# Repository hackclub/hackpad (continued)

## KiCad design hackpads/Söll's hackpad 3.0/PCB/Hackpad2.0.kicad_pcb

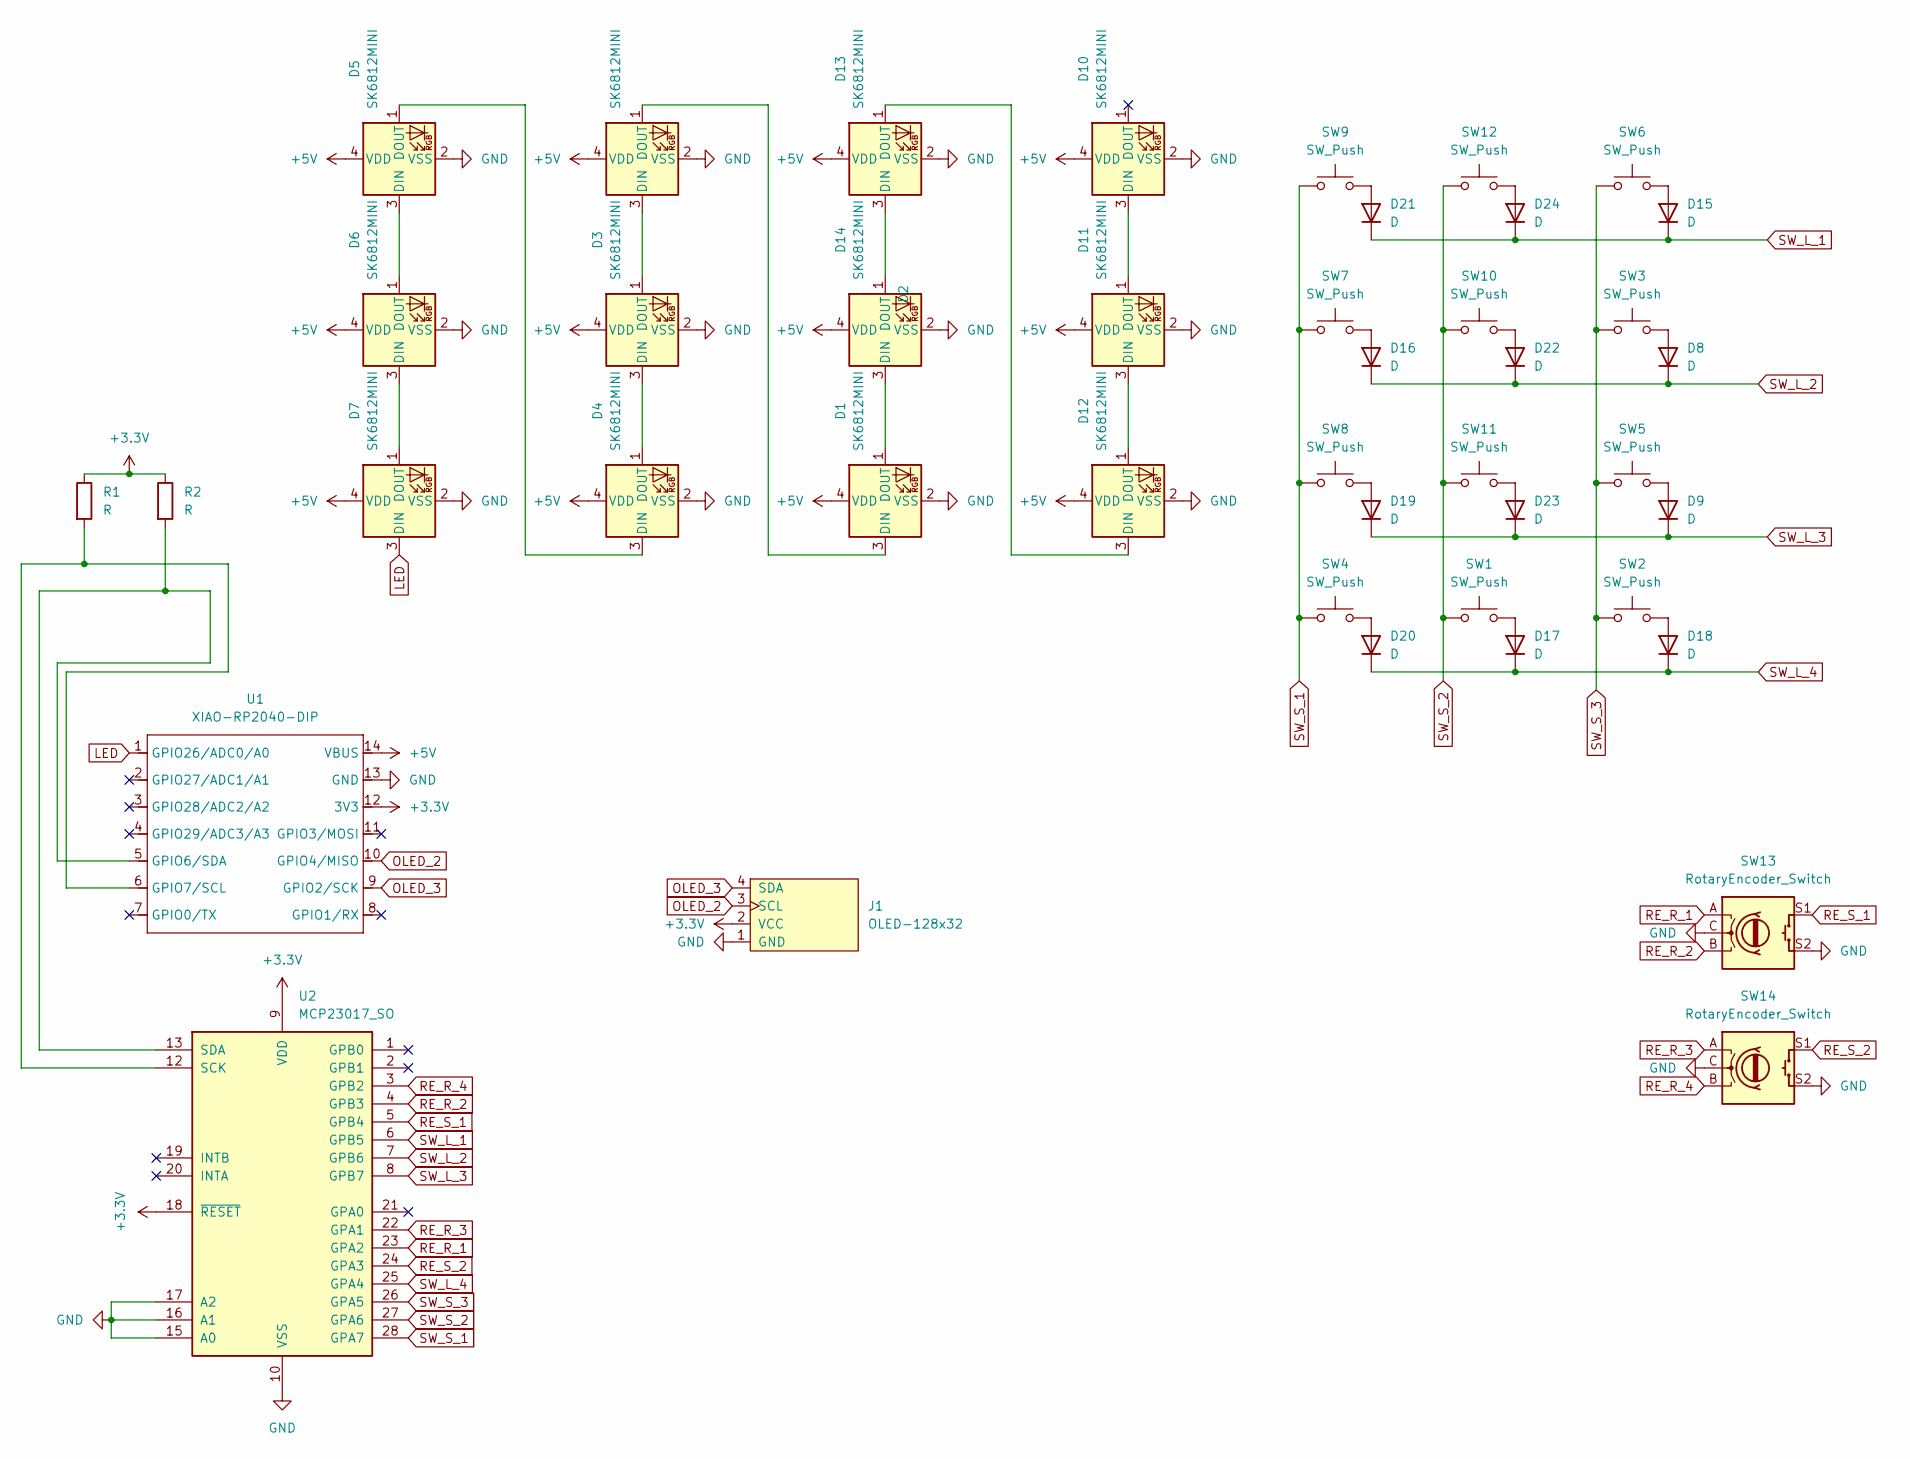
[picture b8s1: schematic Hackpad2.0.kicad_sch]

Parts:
D1, D2, D3, D4, D5, D6, D7, D10, D11, D12, D13, D14: SK6812MINI; LED_SK6812MINI_PLCC4_3.5x3.5mm_P1.75mm
D8, D9, D15, D16, D17, D18, D19, D20, D21, D22, D23, D24: D; D_DO-35_SOD27_P7.62mm_Horizontal
J1: OLED-128x32; SSD1306-0.91-OLED-4pin-128x32
R1, R2: R; R_Axial_DIN0204_L3.6mm_D1.6mm_P7.62mm_Horizontal
SW1, SW2, SW3, SW4, SW5, SW6, SW7, SW8, SW9, SW10, SW11, SW12: SW_Push; SW_Cherry_MX_1.00u_PCB
SW13, SW14: RotaryEncoder_Switch; RotaryEncoder_Alps_EC11E-Switch_Vertical_H20mm_CircularMoun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
U1: XIAO-RP2040-DIP
U2: MCP23017_SO; SOIC-28W_7.5x17.9mm_P1.27mm

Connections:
+3.3V: J1.2 (VCC), R1.1, R2.1, U1.12 (3V3), U2.9 (VDD), U2.18 (~RESET)
+5V: D1.4 (VDD), D2.4 (VDD), D3.4 (VDD), D4.4 (VDD), D5.4 (VDD), D6.4 (VDD), D7.4 (VDD), D10.4 (VDD), D11.4 (VDD), D12.4 (VDD), D13.4 (VDD), D14.4 (VDD), U1.14 (VBUS)
GND: D1.2 (VSS), D2.2 (VSS), D3.2 (VSS), D4.2 (VSS), D5.2 (VSS), D6.2 (VSS), D7.2 (VSS), D10.2 (VSS), D11.2 (VSS), D12.2 (VSS), D13.2 (VSS), D14.2 (VSS), J1.1 (GND), SW13.C, SW13.S2, SW14.C, SW14.S2, U1.13 (GND), U2.10 (VSS), U2.15 (A0), U2.16 (A1), U2.17 (A2)
LED: D7.3 (DIN), U1.1 (GPIO26/ADC0/A0)
unnamed: D1.3 (DIN), D2.1 (DOUT)
unnamed: D1.1 (DOUT), D14.3 (DIN)
unnamed: D2.3 (DIN), D3.1 (DOUT)
unnamed: D3.3 (DIN), D4.1 (DOUT)
unnamed: D4.3 (DIN), D5.1 (DOUT)
unnamed: D5.3 (DIN), D6.1 (DOUT)
unnamed: D6.3 (DIN), D7.1 (DOUT)
unnamed: D8.2 (A), SW3.2
unnamed: D9.2 (A), SW5.2
unnamed: D10.3 (DIN), D11.1 (DOUT)
unnamed: D11.3 (DIN), D12.1 (DOUT)
unnamed: D12.3 (DIN), D13.1 (DOUT)
unnamed: D13.3 (DIN), D14.1 (DOUT)
unnamed: D15.2 (A), SW6.2
unnamed: D16.2 (A), SW7.2
unnamed: D17.2 (A), SW1.2
unnamed: D18.2 (A), SW2.2
unnamed: D19.2 (A), SW8.2
unnamed: D20.2 (A), SW4.2
unnamed: D21.2 (A), SW9.2
unnamed: D22.2 (A), SW10.2
unnamed: D23.2 (A), SW11.2
unnamed: D24.2 (A), SW12.2
unnamed: R2.2, U1.5 (GPIO6/SDA), U2.13 (SDA)
unnamed: R1.2, U1.6 (GPIO7/SCL), U2.12 (SCK)
OLED_2: J1.3 (SCL), U1.10 (GPIO4/MISO)
OLED_3: J1.4 (SDA), U1.9 (GPIO2/SCK)
RE_R_1: SW13.A, U2.23 (GPA2)
RE_R_2: SW13.B, U2.4 (GPB3)
RE_R_3: SW14.A, U2.22 (GPA1)
RE_R_4: SW14.B, U2.3 (GPB2)
RE_S_1: SW13.S1, U2.5 (GPB4)
RE_S_2: SW14.S1, U2.24 (GPA3)
SW_L_1: D15.1 (K), D21.1 (K), D24.1 (K), U2.6 (GPB5)
SW_L_2: D8.1 (K), D16.1 (K), D22.1 (K), U2.7 (GPB6)
SW_L_3: D9.1 (K), D19.1 (K), D23.1 (K), U2.8 (GPB7)
SW_L_4: D17.1 (K), D18.1 (K), D20.1 (K), U2.25 (GPA4)
SW_S_1: SW4.1, SW7.1, SW8.1, SW9.1, U2.28 (GPA7)
SW_S_2: SW1.1, SW10.1, SW11.1, SW12.1, U2.27 (GPA6)
SW_S_3: SW2.1, SW3.1, SW5.1, SW6.1, U2.26 (GPA5)

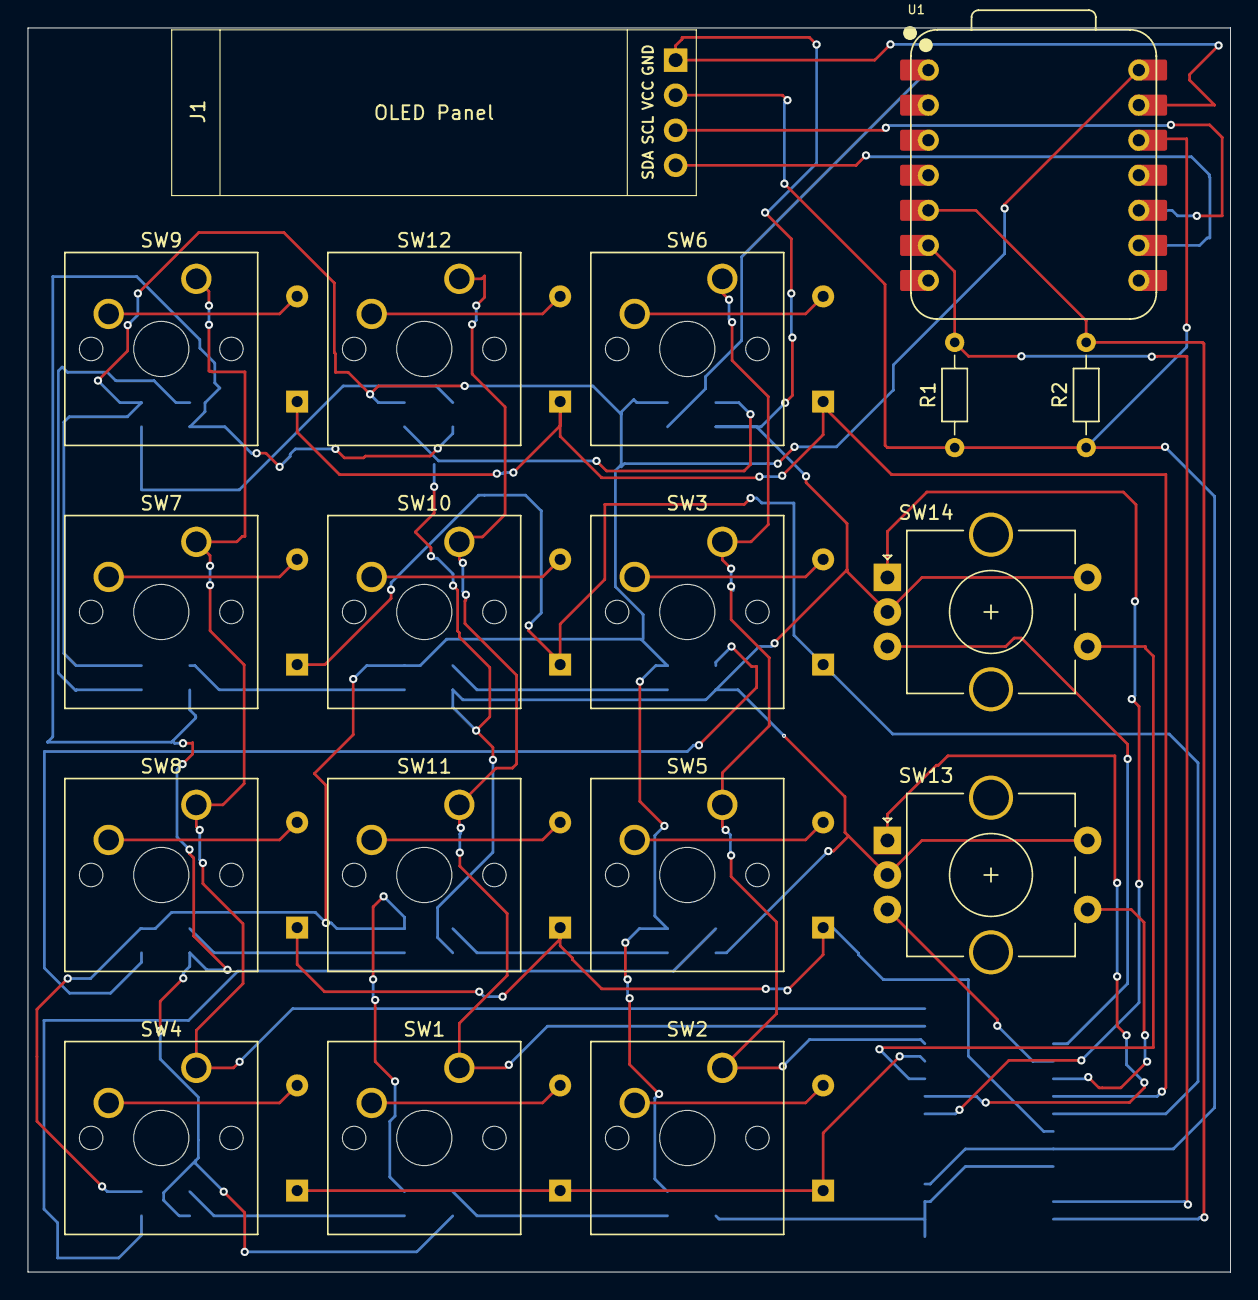
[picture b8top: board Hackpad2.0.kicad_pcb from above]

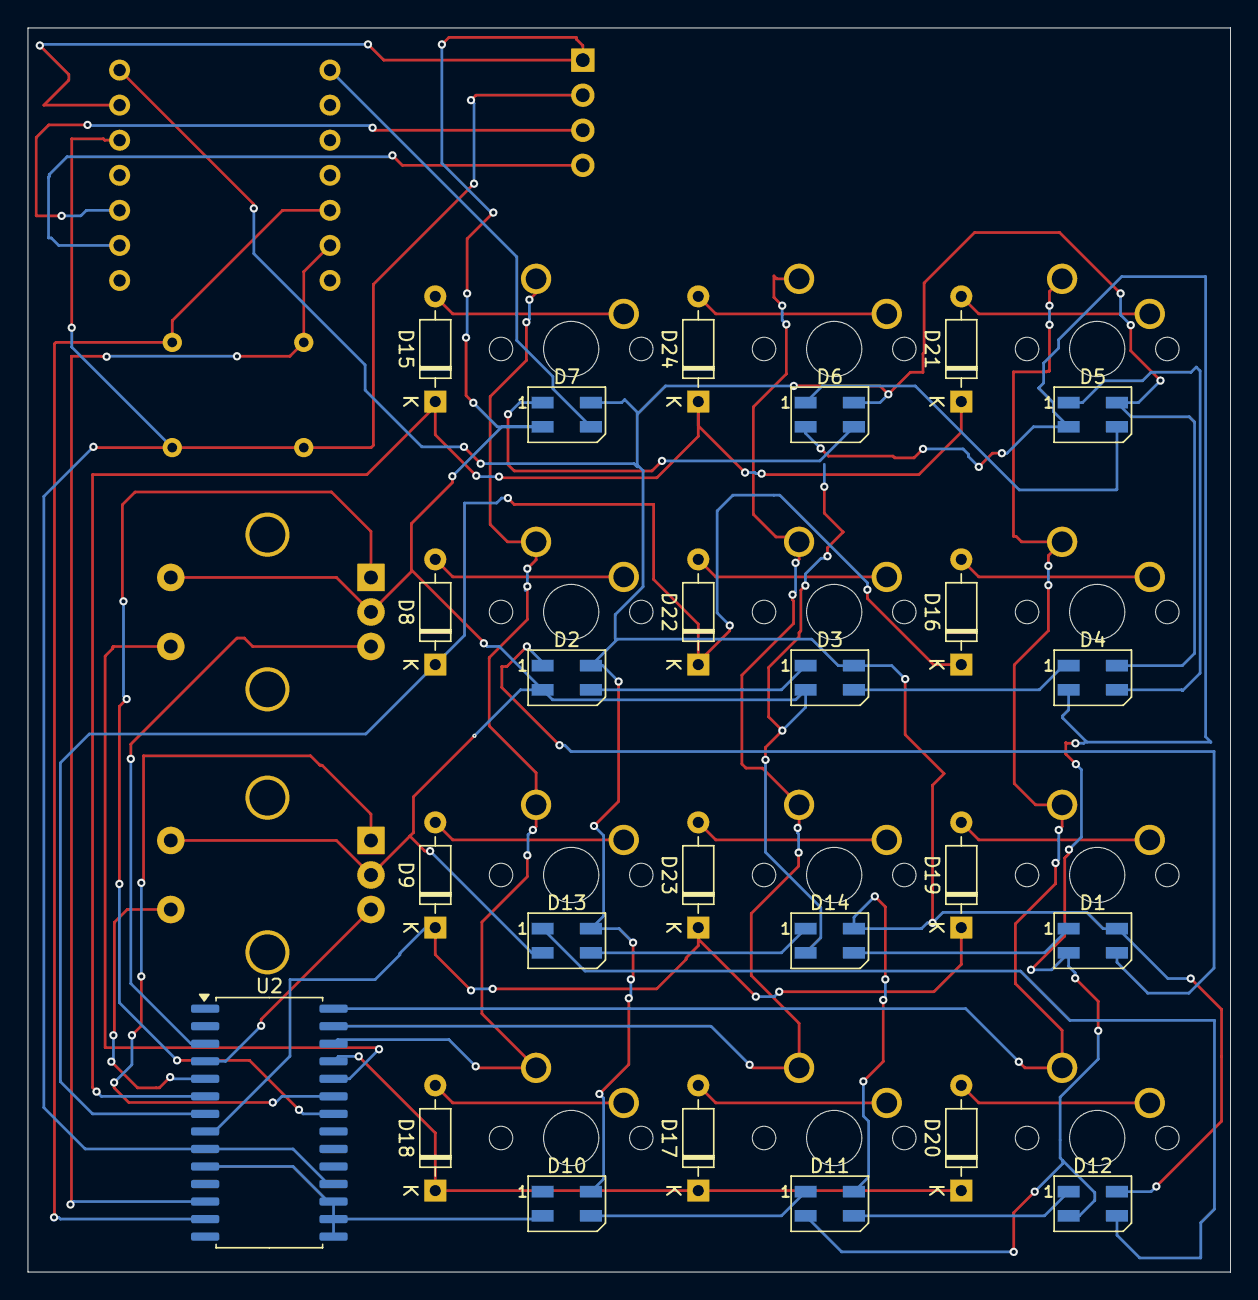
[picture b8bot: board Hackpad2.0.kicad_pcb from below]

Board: 2 copper layers, 87.1 x 90.1 mm, 43 parts (25 on the bottom side), 44 nets.

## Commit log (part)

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2025-03-20 Add Branding to all parts
2025-03-20 update deltaboard
2025-03-21 Krishveer's Hackboard
2025-03-21 remove OLED library
2025-03-21 remove OPL lib
2025-03-21 remove models (1)
2025-03-21 remove models (2)
2025-03-22 Uploaded Hyperboard files
2025-03-22 feat: Add virtual_keyboard
    @virtualfuzz keyboard
2025-03-22 feat: Add link to the original repo
2025-03-22 Added GamerBoard
2025-03-22 added cardgrant page
2025-03-22 revised docs
2025-03-22 updated hackboard
2025-03-22 fixed main.tsx by removign unused imports
2025-03-22 Add OLED cutout
2025-03-22 add oled slit
2025-03-22 update screenshot
2025-03-22 fix the tiny problem in the readme
2025-03-23 Add files via upload
    add text branding on bottom of both cases
2025-03-23 fixed all issues please approve
2025-03-23 remove submodule
2025-03-23 sync submodule
2025-03-23 fix bold text
2025-03-23 add myCompactKeyboard
2025-03-23 add silk screen text for myCompactKeyboard
2025-03-23 Finalise Case (Fix screw and insert issues)
2025-03-24 Pending changes exported from your codespace
2025-03-25 Update midipad with revised version
2025-03-25 Update README.md for midipad
2025-03-26 Adding Barni Keyboard
2025-03-27 BOM update
2025-03-27 Fix accidental deletion
2025-03-29 Fixed tolerances
2025-03-29 Final README.md
2025-03-30 fix: add case opening for usb
2025-03-30 Connect sda/scl for robopad
2025-04-04 fixed bottom shell to print without support
2025-04-05 Updated CAD
2025-04-08 fix: move basmati.step to CAD/
2025-04-09 Revamped Hackpad README, removed unnecessary libraries
2025-04-11 Remodel case in Fusion 360
2025-04-12 Remove libraries from robopad
2025-04-12 fix reame
2025-04-12 endboard
2025-04-14 add ninefold
2025-04-14 Rename macropad.zip to gerber.zip
2025-04-14 Revert "endboard"
    This reverts commit ae698ac5931ae4c96808389b3cca61e4a54952d2.
2025-04-14 Removed extra files
2025-04-20 update deltaboard (fix bugs)
2025-05-01 added kicad pro files
2025-05-02 Add images
2025-05-02 add case images
2025-05-02 remove broken pics
2025-05-03 Add new versions
2025-05-04 Delete hackpads/HexadeciPad/pcb/OPL_Kicad_Library-master directory
    Delete pcb libraries
2025-05-13 Add ghostpad
2025-05-14 edited reqs
2025-05-18 made README.md
2025-05-18 forgot schematic screenshot, so uploaded it
2025-05-20 Add LazyPad hackpad
2025-05-20 add cad zip (step was too big)
2025-05-21 uploaded pcb files
2025-05-21 added gerbers
2025-05-22 updated docs for v3
2025-05-24 Fix broken link in submission page
2025-05-29 updated docs
2025-05-30 reduced the size of the files of pinuspad
2025-06-04 updated site. should be good for v3
2025-06-06 morseboard added this time, no weird git stuff
2025-06-06 readme change, talks more about the inspiration.
2025-06-06 Added BOM.csv
2025-06-08 Correct and improve BOM
2025-06-08 Update and improve BOM
2025-06-10 Add drill files to gerbers.zip
2025-06-11 added new knob file
2025-06-11 moved misplaced hackpad
2025-06-26 Add my hackpad
2025-06-27 Add NormalPad
2025-06-27 Overwrite with new designs
2025-06-27 Fixed?? The images
2025-06-29 Override crappy files with good ones HOPEFULLY LAST TIME
2025-06-29 Fixed images?
2025-07-17 Create CAD
2025-07-17 Add CAD Files
2025-07-17 Create PCB
2025-10-05 Fix formatting of checklist items in Overview.mdx
2025-10-05 Enhance Overview with README and project visuals
    Added sections for README content and project pictures.
2025-10-06 Delete hackpads/ChessPad/PCB/ChessPad_KiCad_Folder/Seeed Studio XIAO Series Library directory
    I was asked to when someone reviewed it, that's all.
2025-10-06 Create file1
2025-10-06 added production stuff
2025-10-11 fixed a typo that pointed beginners to #highway not #blueprint
    As highway is closed, the link now redirects to the blueprint homepage
2025-10-12 added as normal
2025-10-13 refactor(woagpad): replace git submodule with raw src
2025-10-13 refactor(woagpad): replace git submodule with raw src take 2
2025-10-14 removed backups
2025-10-14 Remove libraries
2025-10-15 removed unnecessary files
2025-10-17 fix: spelling
2025-10-18 Enhance README with description and images
    Updated README with a description and new image links.
2025-10-18 I shouldn't have been keeping v1 files
2025-10-18 update firepad files (I thought I did this ages ago oops :/)
2025-10-18 Update README slightly
2025-12-20 Fix expired xdn link
2026-01-23 Fix typo in Tutorial.mdx regarding rectangle placement
2026-02-17 update: clarify formats
2026-03-22 Add WizPad submission by wizrizz
2026-03-22 Add 3D printable case STL
2026-03-22 Fix 100mm rule compliance and high-quality render
2026-03-22 Update to WizPad Ultra Case - Ergonomic High Profile Design
2026-03-22 ULTIMATE UPGRADE: Added OLED Display, Keycaps, and high-detail render
2026-03-25 Fix SK6812MINI-E footprint to stop the model from breaking
2026-04-01 edit spelling
2026-04-04 Fix code block formatting in SimpleTutorial.mdx
    Updated code block formatting for clarity in tutorial.
    In current web site, the last comma isn't appeared:
    ["","",""]
    ↑It should be : ["","",""],
    Because without the last comma, plate generator couldn't work well.
2026-04-09 Bump vite from 5.4.3 to 6.4.2 in /website
    Bumps [vite](https://github.com/vitejs/vite/tree/HEAD/packages/vite) from 5.4.3 to 6.4.2.
    - [Release notes](https://github.com/vitejs/vite/releases)
    - [Changelog](https://github.com/vitejs/vite/blob/v6.4.2/packages/vite/CHANGELOG.md)
    - [Commits](https://github.com/vitejs/vite/commits/v6.4.2/packages/vite)
    ---
    updated-dependencies:
2026-04-24 Bump postcss from 8.4.45 to 8.5.10 in /website
    Bumps [postcss](https://github.com/postcss/postcss) from 8.4.45 to 8.5.10.
    - [Release notes](https://github.com/postcss/postcss/releases)
    - [Changelog](https://github.com/postcss/postcss/blob/main/CHANGELOG.md)
    - [Commits](https://github.com/postcss/postcss/compare/8.4.45...8.5.10)
    ---
    updated-dependencies:
2026-06-04 Add Hexpad macropad submission
2026-06-05 add 404 not found page and wired it into the router as a global catch-all route so unknown paths now show a matching hackpad-style 404 page
2026-06-25 Add LG Hackpad submission
    9-key macropad (XIAO RP2040) with rotary encoder profile-browser and
    OLED, custom PCB (68 x 99.68 mm, 2-layer, DRC clean), no-supports
    3D-printed open case, CircuitPython firmware. First-ever PCB.
